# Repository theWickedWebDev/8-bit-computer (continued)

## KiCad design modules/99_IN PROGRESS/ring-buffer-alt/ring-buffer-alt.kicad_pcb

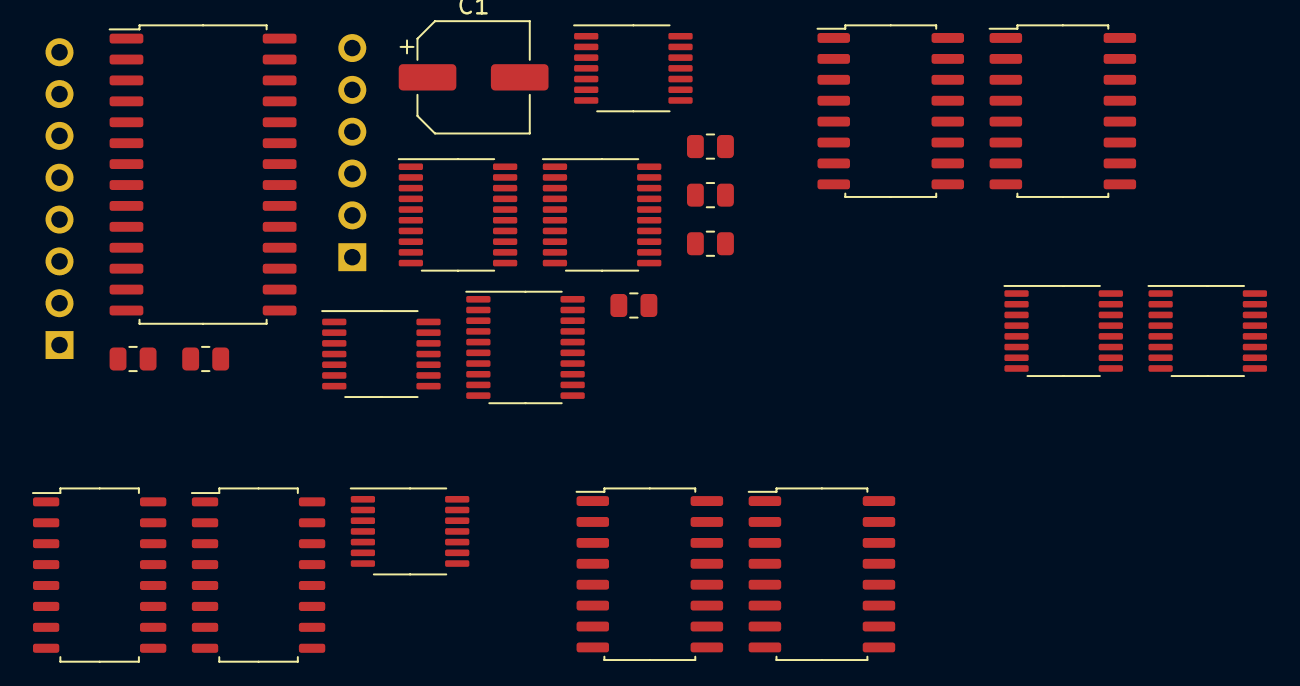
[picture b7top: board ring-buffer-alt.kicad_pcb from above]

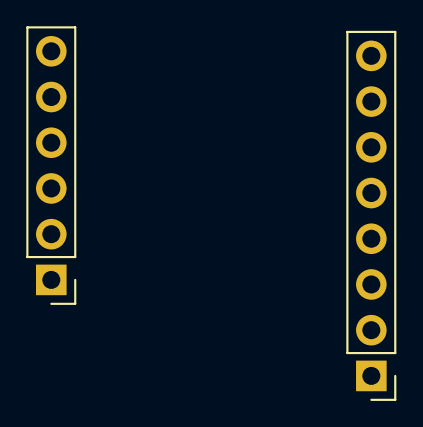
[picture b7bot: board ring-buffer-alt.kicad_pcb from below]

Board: 2 copper layers, 24 parts (2 on the bottom side), 68 nets, no tracks yet.

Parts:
C1: C; CP_Elec_6.3x5.9
J1: Conn_01x06; PinHeader_1x06_P2.54mm_Vertical
J2: Conn_01x08; PinHeader_1x08_P2.54mm_Vertical
R1, R2, R3, R4, R5, R6: R_US; R_0805_2012Metric
U1, U11: 74LS04; TSSOP-14_4.4x5mm_P0.65mm
U2: 74LS00; TSSOP-14_4.4x5mm_P0.65mm
U3, U4, U6: 74HC245; TSSOP-20_4.4x6.5mm_P0.65mm
U5: IS61C64AL; SOIC-28W_7.5x17.9mm_P1.27mm
U7, U8, U9, U10: 74LS193; SO-16_5.3x10.2mm_P1.27mm
U12, U13: 74LS283; SOIC-16_4.55x10.3mm_P1.27mm
U14, U15: 74HC157PW,118; TSSOP-16_4.4x5mm_P0.65mm

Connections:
/Read Counter/~LOAD: C1.1, R1.2, U7.11, U8.11, U9.11, U10.11
BUS0: J2.8, U3.18, U4.18, U6.18
BUS1: J2.7, U3.17, U4.17, U6.17
BUS2: J2.6, U3.16, U4.16, U6.16
BUS3: J2.5, U3.15, U4.15, U6.15
BUS4: J2.4, U3.14, U4.14, U6.14
BUS5: J2.3, U3.13, U4.13, U6.13
BUS6: J2.2, U3.12, U4.12, U6.12
BUS7: J2.1, U3.11, U4.11, U6.11
COUNT_0: U3.2, U12.4
COUNT_1: U3.3, U12.1
COUNT_2: U3.4, U12.13
COUNT_3: U3.5, U12.10
COUNT_4: U3.6, U13.4
COUNT_5: U3.7, U13.1
COUNT_6: U3.8, U13.13
COUNT_7: U3.9, U13.10
GND: C1.2, J1.2, R3.2, R5.2, U1.7, U2.7, U3.10, U4.10, U5.2, U5.14, U5.21, U5.22, U5.23, U5.24, U5.25, U6.1, U6.10, U7.1, U7.8, U7.9, U7.10, U7.14, U7.15, U8.1, U8.8, U8.9, U8.10, U8.14, U8.15, U9.1, U9.8, U9.9, U9.10, U9.14, U9.15, U10.1, U10.8, U10.9, U10.10, U10.14, U10.15, U11.7, U12.8, U13.8, U14.8, U14.15, U15.8, U15.15
IO0: U4.2, U5.11, U6.2
IO1: U4.3, U5.12, U6.3
IO2: U4.4, U5.13, U6.4
IO3: U4.5, U5.15, U6.5
IO4: U4.6, U5.16, U6.6
IO5: U4.7, U5.17, U6.7
IO6: U4.8, U5.18, U6.8
IO7: U4.9, U5.19, U6.9
unnamed: U1.2, U12.6
unnamed: U1.4, U12.2
unnamed: U1.6, U2.2
unnamed: U1.8, U12.11
unnamed: U1.10, U13.6
unnamed: U1.12, U13.2
unnamed: U7.12, U8.5
unnamed: U9.12, U10.5
unnamed: U11.2, U13.15
unnamed: U11.4, U13.11
unnamed: U11.6, U12.15
unnamed: U12.9, U13.7
RAM_ADDR_0: U5.10, U14.4
RAM_ADDR_1: U5.9, U14.7
RAM_ADDR_2: U5.8, U14.9
RAM_ADDR_3: U5.7, U14.12
RAM_ADDR_4: U5.6, U15.4
RAM_ADDR_5: U5.5, U15.7
RAM_ADDR_6: U5.4, U15.9
RAM_ADDR_7: U5.3, U15.12
READ_ADDR_0: U1.1, U7.3, U14.3
READ_ADDR_1: U1.3, U7.2, U14.6
READ_ADDR_2: U7.6, U11.5, U14.10
READ_ADDR_3: U1.9, U7.7, U14.13
READ_ADDR_4: U1.11, U8.3, U15.3
READ_ADDR_5: U1.13, U8.2, U15.6
READ_ADDR_6: U8.6, U11.1, U15.10
READ_ADDR_7: U8.7, U11.3, U15.13
READ_REQUEST: J1.4, R5.1, U2.1
VCC: J1.1, R1.1, R2.1, R4.2, R6.1, U1.14, U2.14, U3.1, U3.20, U4.1, U4.20, U5.28, U6.20, U7.4, U7.16, U8.4, U8.16, U9.4, U9.16, U10.4, U10.16, U11.14, U12.7, U12.16, U13.16, U14.16, U15.16
WRITE_ADDR_0: U9.3, U12.5, U14.2
WRITE_ADDR_1: U9.2, U12.3, U14.5
WRITE_ADDR_2: U9.6, U12.14, U14.11
WRITE_ADDR_3: U9.7, U12.12, U14.14
WRITE_ADDR_4: U10.3, U13.5, U15.2
WRITE_ADDR_5: U10.2, U13.3, U15.5
WRITE_ADDR_6: U10.6, U13.14, U15.11
WRITE_ADDR_7: U10.7, U13.12, U15.14
~BUFFER_EN: J1.6, R3.1, U5.20
~READ_DATA: U2.3, U6.19, U7.5
~STATUS_COUNT_ASSERT: J1.3, R6.2, U3.19
~WRITE_DATA: J1.5, R2.2, R4.1, U1.5, U4.19, U5.27, U9.5, U14.1, U15.1
